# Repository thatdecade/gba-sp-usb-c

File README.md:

# Fork Information

* This fork was created from scratch using Rory Hayes (rorosaurus)'s design as reference. 
* The BOM / part list was altered to use parts that are easy to source on digikey.

Nothing for sale here.  If you would like to purchase a board pre-made, visit [rorosaurus's github project](https://github.com/rorosaurus/gba-sp-usb-c) for links.

## This is Game Boy Advance SP mod to add a handsolderable USB-C port.

The CC resistors make this mod compatible with both common USB A chargers and modern USB C PD / Quick Charge chargers.

# How to Make:

You should be comfortable with a solder iron and have access to a 3D printer.  Hot air re-work station is optional, but recommended.

* Order PCB from OSHPark: https://oshpark.com/shared_projects/b8vKmTIY
   - Click the link or upload the .brd file to OshPark.
   - Select 2oz copper, 0.8mm thickness from the checkout page.
* Order parts from Digikey
   - USB-C port: https://www.digikey.com/en/products/detail/cui-devices/UJC-VP-3-SMT-TR/14310511
   - 5.1K resistors: https://www.digikey.com/en/products/detail/yageo/RC0402FR-135K1L/14286364
* 3D Print the spacer from [Thingiverse](https://www.thingiverse.com/thing:4123563).
* Cleanup: Use sandpaper or dremel to remove burrs from pcb edges.
* Solder smd parts to pcb.
* See [INSTALLATION](INSTALLATION.md) for the next steps.

# Compatibility

This design is ok for the AGS-001 (2003 Front Light) and AGS-101 (2005 Back Light).

# Disclaimer

This project is MIT licensed and comes with no warranty.  Modify your console at your own risk!

# References

* https://github.com/rorosaurus/gba-sp-usb-c/
* https://www.reddit.com/r/GameBoy/wiki/mods
* https://discord.gg/gameboy
* https://docs.oshpark.com/design-tools/eagle/cutouts-and-slots/

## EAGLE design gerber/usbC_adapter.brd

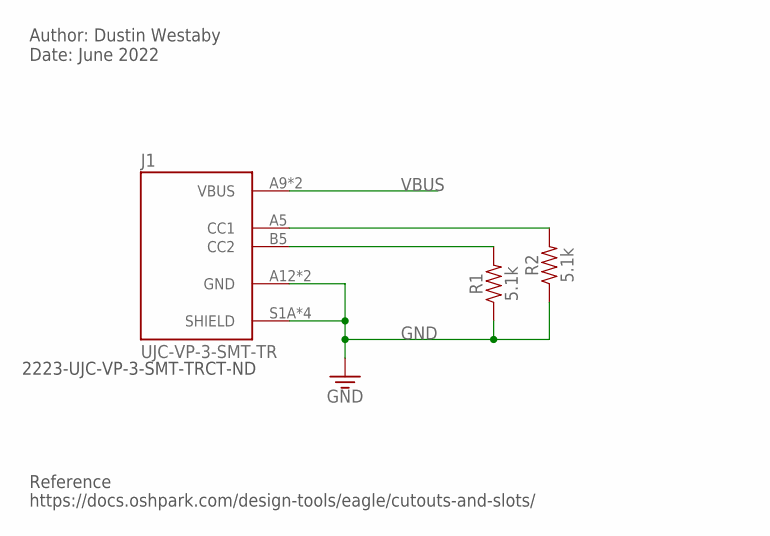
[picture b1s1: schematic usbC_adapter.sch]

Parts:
J1: UJC-VP-3-SMT-TR; CUI_UJC-VP-3-SMT-TR
R1, R2: 5.1k; 0402-TIGHT

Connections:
GND: J1.A12 (GND), J1.B12 (GND), J1.S1A (SHIELD), J1.S1B (SHIELD), J1.S2A (SHIELD), J1.S2B (SHIELD), R1.1, R2.1
unnamed: J1.B5 (CC2), R1.2
unnamed: J1.A5 (CC1), R2.2
VBUS: J1.A9 (VBUS), J1.B9 (VBUS)

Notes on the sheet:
2223-UJC-VP-3-SMT-TRCT-ND
https://docs.oshpark.com/design-tools/eagle/cutouts-and-slots/
Reference
Author: Dustin Westaby Date: June 2022

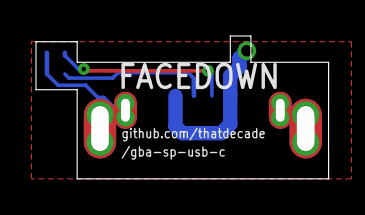
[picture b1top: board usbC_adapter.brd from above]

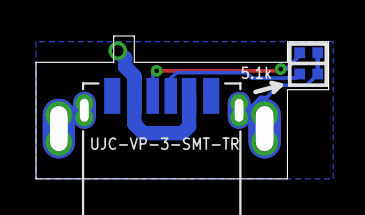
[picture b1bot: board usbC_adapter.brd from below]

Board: 2 copper layers, 15.3 x 6.9 mm, 3 parts (3 on the bottom side), 4 nets.

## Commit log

2022-06-27 Cleanup
2022-06-27 Create LICENSE
2022-06-27 Repo updated with my files.
2022-06-27 Removed old files
2022-06-27 Updated oshpark link
2022-06-27 added affiliate note

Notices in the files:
parts and their libraries:
SparkFun-Resistors: Licensing: Creative Commons ShareAlike 4.0 International - https://creativecommons.org/licenses/by-sa/4.0
